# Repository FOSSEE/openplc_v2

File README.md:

[OpenPLC](https://openplc.fossee.in/) _model 2_ development documentation.

Contact by [mail](mailto:contact-openplc@fossee.in) for details.

> NOTE: the project is a work in progress.

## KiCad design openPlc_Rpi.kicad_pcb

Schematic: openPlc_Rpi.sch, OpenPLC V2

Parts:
C1: 100nf; C_0805_2012Metric
C2: 150uf; CP_Elec_8x10
C3: 1000uf; CP_Elec_10x10
C4: 100n; C_0805_2012Metric
C5, C6: 22uf; C_0805_2012Metric
C7: .33uf; C_1206_3216Metric_Pad1.42x1.75mm_HandSolder
C8: .1uf; C_0805_2012Metric
C9: 1uf; C_0805_2012Metric_Pad1.15x1.40mm_HandSolder
D1, D2, D3, D4, D7, D8, D9, D10: D_Zener; D_1206_3216Metric
D5: NTS245SF; D_SMA_Handsoldering
D6: B340; D_SMC
D11, D12, D13, D14, D15, D16, D17, D18: LED; LED_0805_2012Metric
D19: S1BB; D_SMB
D20: LED_ALT; LED_0805_2012Metric
D21, D22: LED; LED_0805_2012Metric_Pad1.15x1.40mm_HandSolder
J1: Raspberry_Pi_2_3; Raspberry_Pi_Zero_FaceUp_SingleMountingHole
J2: Screw_Terminal_01x04; TerminalBlock_Phoenix_MKDS-1,5-4-5.08_1x04_P5.08mm_Horizont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
J3, J8, J9: Screw_Terminal_01x02; TerminalBlock_Phoenix_MKDS-1,5-2-5.08_1x02_P5.08mm_Horizont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
J4, J6: bergStrip_01x06_Male; bergStrip_male_1x06_P2.54mm_Vertical
J5, J7: Screw_Terminal_01x12; TerminalBlock_Phoenix_MKDS-1,5-12-5.08_1x12_P5.08mm_Horizon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
J10, J11, J12, J13: Conn_01x04; JST_XH_B4B-XH-A_1x04_P2.50mm_Vertical
J14: Screw_Terminal_01x10; TerminalBlock_Phoenix_MKDS-1,5-10-5.08_1x10_P5.08mm_Horizon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
J15, J16: bergStrip_01x04_Male; bergStrip_1x04_P2.54mm_Vertical
K1, K2, K3, K4, K5, K6, K7, K8: G5LE-1; Relay_SPDT_Omron-G5LE-1
L1: 680uh; L_12x12mm_H6mm
Q1: BSS123; SOT-23
Q2, Q3: 2N7002; SOT-23
R1, R2, R3, R4, R5, R6, R7, R8, R9, R10, R11, R12, R17, R18, R19, R20, R21, R22, R23, R24, R25, R26, R27, R28, R29, R30, R31, R32, R41, R42, R43, R45: 10k; R_0805_2012Metric_Pad1.15x1.40mm_HandSolder
R13, R14, R15, R16: 5k; R_0805_2012Metric_Pad1.15x1.40mm_HandSolder
R33, R34, R35, R36, R37, R38, R39, R40: 220R; R_0805_2012Metric_Pad1.15x1.40mm_HandSolder
R44: 120R; R_0805_2012Metric_Pad1.15x1.40mm_HandSolder
R46: 220; R_0805_2012Metric_Pad1.15x1.40mm_HandSolder
R47, R48: 510R; R_0805_2012Metric_Pad1.15x1.40mm_HandSolder
U1: power_LM2576; TO-263-5_TabPin3
U2, U3: LTV-847; DIP-16_W8.89mm_SMDSocket_LongPads
U4: power_L7812_smd; TO-263-2
U5: MAX481E; SOIC-8_3.9x4.9mm_P1.27mm
U6: ADS1018IDGS; TSSOP-10_3x3mm_P0.5mm
U7: AMS1117-3.3; SOT-223-3_TabPin2
U8: ULN2803A; SOIC-18W_7.5x11.6mm_P1.27mm

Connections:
+3V3: C6.1, C9.1, J1.1, J1.17, R17.2, R18.2, R19.2, R20.2, R29.2, R30.2, R31.2, R32.2, R42.2, R43.2, R47.1, R48.1, U5.8 (VCC), U7.2 (VO)
+5V: C1.1, C3.1, C5.1, D1.1, D2.1, D3.1, D4.1, D7.1, D8.1, D9.1, D10.1, J1.2, J1.4, J4.6, J6.6, J10.3, J11.3, J12.3, J13.3, K1.5, K2.5, K3.5, K4.5, K5.5, K6.5, K7.5, K8.5, L1.2, R33.2, R34.2, R35.2, R36.2, R37.2, R38.2, R39.2, R40.1, R46.2, U1.4, U7.3 (VI), U8.10
+12V: C8.1, D19.1, J10.2, J11.2, J12.2, J13.2, U4.3
+24V: C2.1, C7.1, D5.1, D19.2, J3.2, J10.1, J11.1, J12.1, J13.1, U1.1, U4.1
/1: J5.10, K1.3
/2: J5.11, K1.1
/3: J5.12, K1.4
/4: J5.7, K2.3
/5: J5.8, K2.1
/6: J5.9, K2.4
/7: J5.4, K3.3
/8: J5.5, K3.1
/9: J5.6, K3.4
/10: J5.1, K4.3
/11: J5.2, K4.1
/12: J5.3, K4.4
/13: J7.10, K5.3
/14: J7.11, K5.1
/15: J7.12, K5.4
/16: J7.7, K6.3
/17: J7.8, K6.1
/18: J7.9, K6.4
/19: J7.4, K7.3
/20: J7.5, K7.1
/21: J7.6, K7.4
/22: J7.1, K8.3
/23: J7.2, K8.1
/24: J7.3, K8.4
/A: J9.1, R44.1, R45.2, U5.6 (A)
/B: J9.2, R43.1, R44.2, U5.7 (B)
/DIGND: J14.5, J14.10, R5.1, R6.1, R7.1, R8.1, R25.1, R26.1, R27.1, R28.1, U2.2, U2.4, U2.6, U2.8, U3.2, U3.4, U3.6, U3.8
/RXD: J1.10, Q3.1 (G), U5.1 (RO)
/TXD: J1.8, Q2.1 (G), R41.2, U5.4 (DI)
CS0: J1.24, U6.2
DI_0: J1.37, R20.1, U2.10
DI_1: J1.35, R19.1, U2.12
DI_2: J1.33, R18.1, U2.14
DI_3: J1.31, R17.1, U2.16
DI_4: J1.29, R32.1, U3.10
DI_5: J1.15, R31.1, U3.12
DI_6: J1.13, R30.1, U3.14
DI_7: J1.11, R29.1, U3.16
DO_0: J1.40, J16.1, U8.8
DO_1: J1.38, J16.2, U8.7
DO_2: J1.36, J16.3, U8.6
DO_3: J1.32, J16.4, U8.5
DO_4: J1.26, J15.1, U8.4
DO_5: J1.22, J15.2, U8.3
DO_6: J1.18, J15.3, U8.2
DO_7: J1.16, J15.4, U8.1
GND: C1.2, C2.2, C3.2, C4.2, C5.2, C6.2, C7.2, C8.2, C9.2, D5.2, D6.2, D20.1, D21.1 (K), D22.1 (K), J1.6, J1.9, J1.14, J1.20, J1.25, J1.30, J1.34, J1.39, J3.1, J4.5, J6.5, J10.4, J11.4, J12.4, J13.4, Q1.2 (S), Q2.2 (S), Q3.2 (S), R13.1, R14.1, R15.1, R16.1, R45.1, U1.3, U1.5, U2.9, U2.11, U2.13, U2.15, U3.9, U3.11, U3.13, U3.15, U4.2, U5.5 (GND), U6.3, U7.1 (GND), U8.9
MISO: J1.21, U6.9
MOSI: J1.19, U6.10
unnamed: C4.1, U6.8
unnamed: D1.2, D15.1, K1.2, U8.14
unnamed: D6.1, L1.1, U1.2
unnamed: D10.2, D14.1, K8.2, U8.15
unnamed: D7.2, D11.1, K5.2, U8.18
unnamed: D11.2, R33.1
unnamed: D8.2, D12.1, K6.2, U8.17
unnamed: D12.2, R34.1
unnamed: D9.2, D13.1, K7.2, U8.16
unnamed: D13.2, R35.1
unnamed: D14.2, R36.1
unnamed: D15.2, R37.1
unnamed: D2.2, D16.1, K2.2, U8.13
unnamed: D16.2, R38.1
unnamed: D3.2, D17.1, K3.2, U8.12
unnamed: D17.2, R39.1
unnamed: D4.2, D18.1, K4.2, U8.11
unnamed: D18.2, R40.2
unnamed: D20.2, R46.1
unnamed: D21.2 (A), Q2.3 (D), R47.2
unnamed: D22.2 (A), Q3.3 (D), R48.2
unnamed: J2.1, R9.1
unnamed: J2.2, R10.1
unnamed: J2.3, R11.1
unnamed: J2.4, R12.1
unnamed: Q1.1 (G), R41.1
unnamed: Q1.3 (D), R42.1, U5.2 (~RE), U5.3 (DE)
unnamed: R1.2, R5.2, U2.1
unnamed: R2.2, R6.2, U2.3
unnamed: R3.2, R7.2, U2.5
unnamed: R4.2, R8.2, U2.7
unnamed: R10.2, R14.2, U6.5
unnamed: R11.2, R15.2, U6.6
unnamed: R12.2, R16.2, U6.7
unnamed: R9.2, R13.2, U6.4
unnamed: R21.2, R25.2, U3.1
unnamed: R22.2, R26.2, U3.3
unnamed: R23.2, R27.2, U3.5
unnamed: R24.2, R28.2, U3.7
SCK: J1.23, U6.1
SCL: J1.5, J8.2
SDA: J1.3, J8.1
in_1: J6.1, J14.1, R21.1
in_2: J6.2, J14.2, R22.1
in_3: J6.3, J14.3, R23.1
in_4: J6.4, J14.4, R24.1
in_5: J4.1, J14.6, R1.1
in_6: J4.2, J14.7, R2.1
in_7: J4.3, J14.8, R3.1
in_8: J4.4, J14.9, R4.1

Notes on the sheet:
OpenPLC V2
Inputs
Outputs
ADC
RasperryPi Zero/w
Two Wire / I2C
b340
Power
RS485

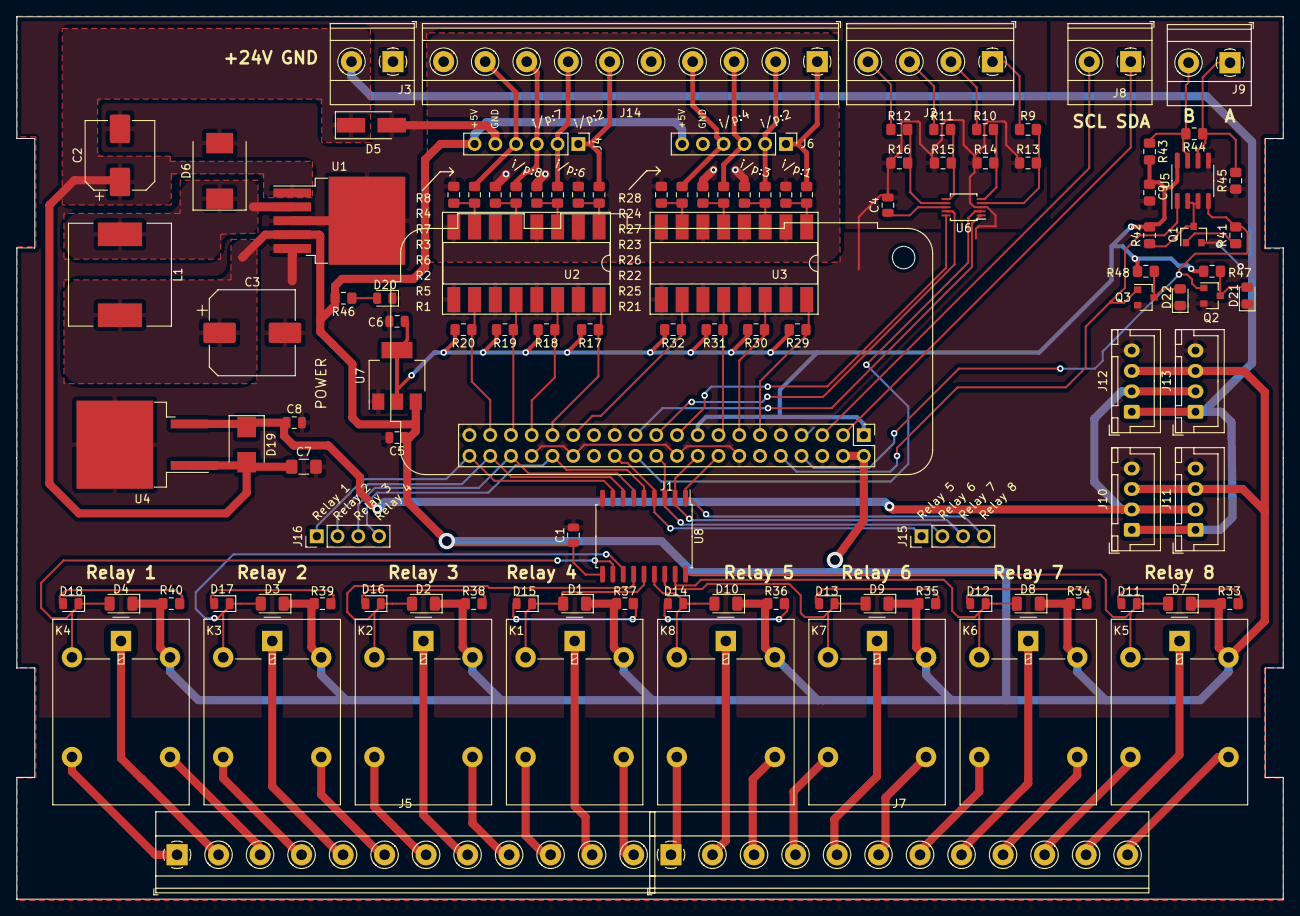
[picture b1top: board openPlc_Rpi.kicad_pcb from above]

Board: 2 copper layers, 155.0 x 108.0 mm, 115 parts (0 on the bottom side), 103 nets.

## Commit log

2019-04-26 April 26th 2019
2019-04-26 added .gitignore file
2019-12-30 [vishnu] unknown
2019-12-30 [vishnu] trial commit in branch working
2019-12-30 [vishnu] created branch revision_0 and first commit to it.
2020-01-06 initial push to GitLab
2020-01-06 fixed untracked files
2020-01-06 [vishnu] fixed untracked files
2020-01-06 [vishnu]cleaned the schematics.
2020-01-06 [vishnu] updated gitignore
2020-01-06 [vishnu] removed local folder sync cript from tracking
2020-01-07 [vishnu] added README
2020-01-21 [vishnu] - remapped the pins for the correct/new orintation of RPi - added the new mapping in the technical document
2020-01-21 [vishnu] - removed the test circuit from the scematic
2020-01-21 [vishnu] Corrected all footpronts to the present library version; PCB not updated.
2020-01-30 [vishnu] created new standalone library for the project with all the necessary components and corresponding footprints.
2020-01-31 [vishnu] Udated library - added LED 0805 symbol and footprint - removed aliases from library leaving just the required components
2020-01-31 [vishnu] replaced Rpi symbol and footprint in schematic and pcb from the new library
2020-02-01 [vishnu] replaced ADC circuit with new library components : scehmatic and PCB updated
2020-02-03 [vishnu] Replaced all component in the POWER circuitry with local library components. Added tantalum, C_1206, AMS117 and ls812 parts to the library.
2020-02-03 [vishnu] Replaced all components in the OUTPUT circuit with local library "fossee_openplc" parts. Deleted an outdated folder with SVG of the older version of the PCB.
2020-02-03 [vishnu] Replaced INPUT circuit with "fossee_openplc" components. Added *-bak and *.bash to gitignore.
2020-02-03 [vishnu] .gitignore fix
2020-03-05 [easwaran] rough draft of routing for new orientation completed with no unconnected ratnests.
2020-03-05 [vishnu] removed tracking of /bom folder. Have reset the cache for the same.
2020-03-06 [vishnu] LICENCE file added.
2020-05-27 [vishnu] - removed copper pours around relay input for better AC isolation. - did DRC and connected the missing labels of digital inputs.
2020-05-27 [vishnu] reordered i/p resistors. Added berg strips to local library.
2020-05-29 [vishnu] added rpi 3d step models. moved opto and added the headers. updated the netlist.
2020-05-29 [vishnu] removed evrything except step file of rpi.
2020-06-01 [vishnu] Added male headers at input and output. PCB updated. Labels updated.
